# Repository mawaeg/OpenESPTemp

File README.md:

# OpenESPTemp

**OpenESPTemp** is an open-source, battery-powered temperature and environmental monitoring sensor built using an ESP32-C6 and a BME280 sensor. It is designed for integration into IoT systems.

The PCB is designed to operate with a rechargeable LiFePo4 AA battery. This repository includes the PCB design, a 3D-printable case, and basic firmware.

<div style="display: flex;">

</div>

---

## ✨ Features

- **Temperature Monitoring**: Provides readings using the BME280 sensor.
- **Environmental Sensing**: Includes humidity and pressure measurements.
- **Low Power**: Optimized for battery-powered operation (under 200nA power consumption while sleeping).
- **Battery Monitoring**: Allows monitoring of the battery voltage.
- **ESP32-C6 Microcontroller**: Handles wireless communication and processing.
- **Customizable PCB**: Features a Qwiic connector and the option to use an LDO when not using a LiFePo4 battery.
- **Open Source**: Fully customizable for specific use cases.
- **OTA updates**: Possibility to update the firmware over the air using ElegantOTA

---

## 🚀 Getting Started

### 1. The PCB

The PCB can be ordered from any PCB manufacturer (e.g., JLCPCB). It can be ordered as single boards or in panels of 5.

- **Manufacturing Files & BOM**: Included in the latest release. The Interactive HTML BOM (iBOM) is recommended for manual assembly.
- **SMT Assembly**: If using an SMT service, you will need to generate the BOM and position files yourself.

> **💡 Note:** You will need two Keystone 53 battery contacts; the BOM only mentions one.

### 2. Additional Parts

| Part | Quantity | Recommendation / Link | Note |
| :--- | :---: | :--- | :--- |
| **LiFePo4 AA (14500) battery (!Normal AA batteries won't work!)** | 1 | [LiFePo4 battery](https://de.aliexpress.com/item/1005005870958670.html?spm=a2g0o.store_pc_home.promoteWysiwyg_2003671164534.1005005870958670&gatewayAdapt=glo2deu) | Any 3.2V LiFePo4 battery should work |
| **3D Printing Filament (PETG)** | ~50g | [White PETG Filament](https://www.nobufil.com/product-page/filament-petg-white) | |
| **UART to USB Adapter** | 1 | [CP2102 Adapter](https://de.aliexpress.com/item/1005006742102516.html?pdp_npi=4%40dis%21EUR%21%E2%82%AC%201%2C97%21%E2%82%AC%200%2C99%21%21%212.28%211.14%21%40211b876717711633668585571ecf24%2112000038159199244%21sh%21DE%210%21X&spm=a2g0o.store_pc_allItems_or_groupList.new_all_items_2007567450475.1005006742102516&gatewayAdapt=glo2deu) | |
| **Pogo Pin Adapter** *(Optional)* | 1 | [4-Pin Prototyping Clamps](https://de.aliexpress.com/item/1005007887384238.html?pdp_npi=4%40dis%21EUR%21%E2%82%AC%2014%2C91%21%E2%82%AC%209%2C69%21%21%21119.18%2177.45%21%4021039ceb17711632823162636ed91c%2112000042738795008%21sh%21DE%216135611440%21X&spm=a2g0o.store_pc_home.allitems_choice_2009265069263.1005007887384238&gatewayAdapt=glo2deu) | Avoids soldering to test points. |

---

## 🛠️ Hardware Assembly

1. **Prepare the PCB**: Solder the components onto the PCB (if not using an SMT service).
   > **ℹ️ Info:** The LDO Solder Jumper is pre-closed for LiFePO4 battery use. If you choose to install an LDO, ensure you cut/open the jumper first.

   > **💡 Note:** If using a Pogo Adapter to flash the firmware, it should be flashed before mounting the battery holders, as the battery holder blocks access to the pins with the adapter.
2. **Print the Case**: Print using standard settings with a 0.2 mm layer height -  no supports needed.
   - The case does not require any screws, it holds together with snap connections
3. **Flash the Firmware**: Follow the instructions below to flash, and configure Wi-Fi/REST endpoint.
4. **Insert the Battery**:
   > **🛑 Warning:** Check the polarity carefully. Never connect the USB to UART adapter and the battery at the same time.
5. **Wake**: Press the WAK button for about a second. The sensor will start sending data periodically.

<div style="display: flex; gap: 20px;">

</div>

---

## 💻 Firmware

By default, the sensor connects to a specified Wi-Fi network and sends data to a REST API endpoint every 15 minutes.

The firmware also allows to update itself using Over The Air updates using [ElegantOTA](https://github.com/ayushsharma82/ElegantOTA).
Read more about that [here](#flash-using-ota-update).

> **💡 Note:** Newer [releases](https://github.com/mawaeg/OpenESPTemp/releases) include a pre-compiled `.bin` file. If you use this, you can skip the compilation step.

### Compiling (PlatformIO)

The firmware can be compiled and flashed with [PlatformIO](https://platformio.org/). You can build in debug mode (to get Serial debug information) or release mode:

```bash
# Debug mode
platformio run --environment esp32-c6-debug

# Release mode
platformio run --environment esp32-c6
```

The firmware has to be flashed via the Serial Interface once. Afterwards it can be updated with [OTA updates](#flash-using-ota-update).

### Flashing

**Wiring:** Connect the UART to USB adapter to the PCB:

| UART Adapter | Direction | PCB | Note |
| :--- | :---: | :--- | :--- |
| **3V3** | ⟷ | **3V3** | Use 3.3V only (do not use 5V) |
| **GND** | ⟷ | **GND** | Common ground is required |
| **TX** | ⟶ | **RX** | Connect Transmit to Receive |
| **RX** | ⟵ | **TX** | Connect Receive to Transmit |

> **ℹ️ Info:** Remember to **cross** the data lines! The **TX** (Transmit) pin on the adapter must connect to the **RX** (Receive) pin on the PCB, and vice versa.

> **🛑 Warning:** You must disconnect the battery before connecting the UART to USB adapter!

#### Option A: Flashing via PlatformIO
Run the following command:
```bash
platformio run --target upload --environment esp32-c6
```
When `Looking for upload port...` appears in the console, put the ESP32 into boot mode:
1. Push the Reset and Boot buttons at the same time.
2. Release the Reset button while keeping the Boot button pressed.
3. The upload will start; release the Boot button.

#### Option B: Flashing via esptool (Precompiled Binary)
Flash the binary using [esptool](https://github.com/espressif/esptool):
```bash
python -m esptool --chip esp32-c6 --port <your-port> --baud 460800 write_flash -z 0x1000 firmware.bin
```
*(Put the ESP32 into boot mode as described above, and replace `<your-port>` with the correct serial port.)*

### Flash using OTA update

The firmware allows to update itself via OTA updates. For that to work the firmware has to be flashed via UART initially.

This is how to trigger a OTA update.
1. Follow steps 1 and 2 of [Reconfigure the device](#reconfigure-the-device)
4. Open **`http://192.168.4.1/update`** in a browser.
5. Here you can upload a new binary (Either get it from the [releases page](https://github.com/mawaeg/OpenESPTemp/releases) or compile it yourself as described [here](#compiling-(platformio))).
6. When uploading while powered by battery you should press and hold the WAK button during the update

---

## ⚙️ Configuration

After flashing, press the Reset button once to start the firmware. If unconfigured, the device will create a Wi-Fi network for setup:

1. Connect to the **`OpenESPTemp Configurator`** Wi-Fi network.
2. Open **`http://192.168.4.1`** in a browser.
3. Configure the following fields in the form:
   - **SSID**: Target Wi-Fi network name.
   - **Password**: Target Wi-Fi network password.
   - **Post URL**: The URL for the POST request.
   - **Authorization**: The Bearer token for authentication (do not include "Bearer", only the token).
4. Click submit. The configuration will be saved, and the device will restart.
5. The sensor will now operate as expected.

### Reconfigure the device

To reconfigure the OpenESPTemp after it has already been configured once, you need do the following:
1. Bring the OpenESPTemp in config mode:
   1. When connected to UART: Press and hold FCT button and press RST shortly. Release FCT after ~6 seconds
   2. When running with battery: Press and hold FCT button and press WAK for around a second. Release FCT after ~6 seconds
2. The OpenESPTemp will create a network called  **`OpenESPTemp Configurator`**. Connect to it.
3. Open **`http://192.168.4.1`** in a browser an reconfigure the fields. Refer to [⚙️ Configuration](#⚙️-configuration)

---

## ⚡ Power consumption

The OpenESPTemp aims to have a very low power consumption.

During sleep, the power consumption is below 200nA (200nA is the limit of the PPK 2, it is probably at around 50nA according to the RV3028-C7 datasheet):

The power consumption for a whole cycle (15 min with sending data once) looks like this:

The power consumption for active mode (sending data) looks the following:

---

## 📐 PCB Design

The PCB was created using KiCad 9.0, the project files are located under [/electronics](/electronics).

The power latch used in this design was inspired by [this](https://circuitcellar.com/resources/quickbits/soft-latching-power-circuits/) article.

To generate a panel yourself using the provided script:
1. Install [KiKit](https://github.com/yaqwsx/KiKit).
2. Execute `/electronics/panelize.sh`.

The panel with the existing config looks like this:

---

## 🧊 CAD

The case was created using Onshape. To edit the case yourself click [here](https://cad.onshape.com/documents/398f777c8db5f4a69ffcddaa/w/b07485d077929fc2f0119cac/e/3395ca67b8682bc329248728?configuration=List_Cy8et1WFmB3Iby%3DDefault&renderMode=0&uiState=699202edfa46508150bca706) and copy the project.

The current STL files are included in the repo under [/cad](/cad).

---

## 🚧 Troubleshooting

TBD

---

## 🗺️ Coming Next

- [ ] Include mounting bracket for the case
- [ ] Include HomeAssistant integration

---

## 📄 License

This project is licensed under the GNU General Public License v3.0. See the [LICENSE](LICENSE) file for details.

### Hardware Libraries
Various libraries were used to create the PCB. Copies of most libraries are included in `/electronics/libs/` to ensure the KiCad project works without manual installation.

Some of these libraries are licensed under their respective licenses. Please review the `README.md` file in the library folders.

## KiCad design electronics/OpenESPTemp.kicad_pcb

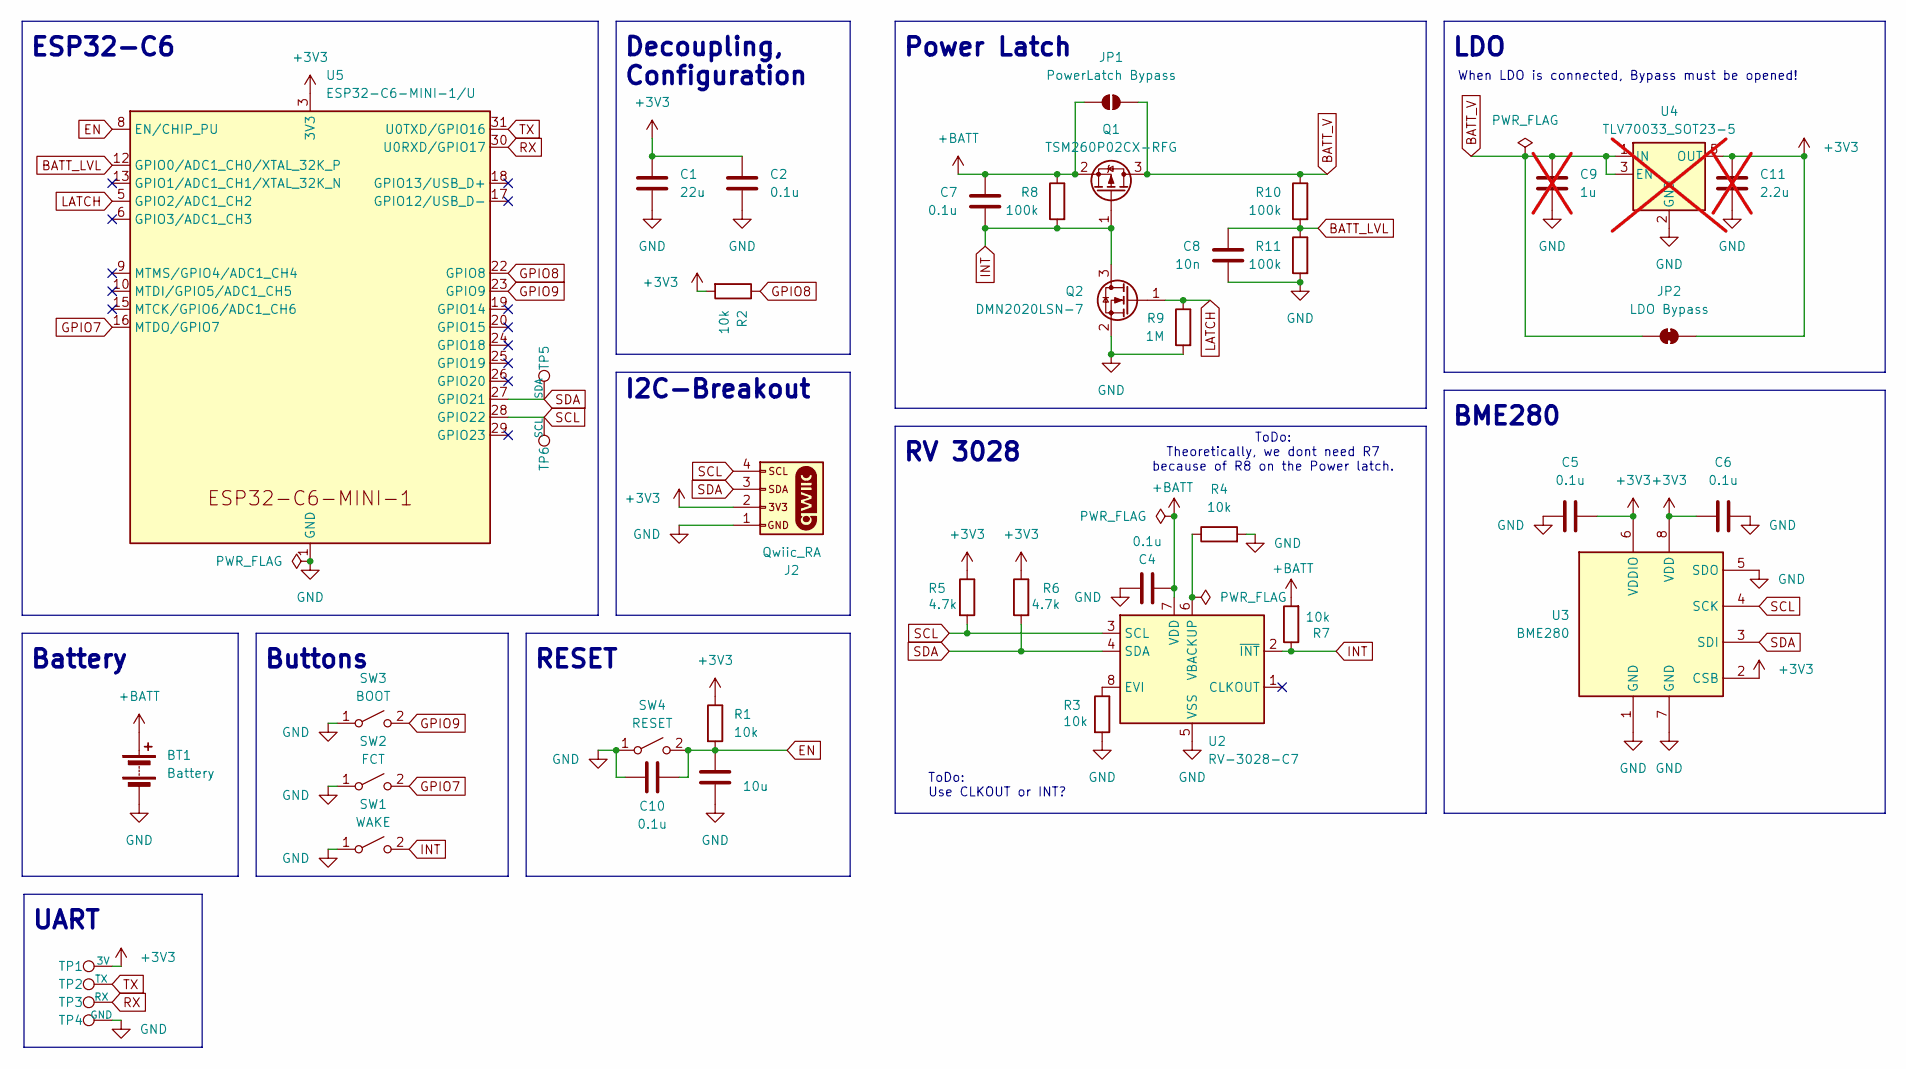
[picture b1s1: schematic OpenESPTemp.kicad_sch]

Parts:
BT1: Battery; Keystone_53_Dual
C1: 22u; C_0603_1608Metric
C2, C4, C5, C6, C7, C10: 0.1u; C_0603_1608Metric
C3: 10u; C_0603_1608Metric
C8: 10n; C_0603_1608Metric
C9: 1u; C_0603_1608Metric; not fitted
C11: 2.2u; C_0603_1608Metric; not fitted
J2: Qwiic_RA; JST_1x04_P1.0mm_Horizontal_SMD
JP1: PowerLatch Bypass; SolderJumper-2_P1.3mm_Open_RoundedPad1.0x1.5mm
JP2: LDO Bypass; SolderJumper-2_P1.3mm_Bridged_RoundedPad1.0x1.5mm
Q1: TSM260P02CX-RFG; SOT-23
Q2: DMN2020LSN-7; SOT-23
R1, R2, R3, R4, R7: 10k; R_0603_1608Metric
R5, R6: 4.7k; R_0603_1608Metric
R8, R10, R11: 100k; R_0603_1608Metric
R9: 1M; R_0603_1608Metric
SW1: WAKE; SW_SPST_B3U-1000P
SW2: FCT; SW_SPST_B3U-1000P
SW3: BOOT; SW_SPST_B3U-1000P
SW4: RESET; SW_SPST_B3U-1000P
TP1: 3V; TestPoint_Pad_D1.5mm
TP2: TX; TestPoint_Pad_D1.5mm
TP3: RX; TestPoint_Pad_D1.5mm
TP4: GND; TestPoint_Pad_D1.5mm
TP5: SDA; TestPoint_Pad_D1.5mm
TP6: SCL; TestPoint_Pad_D1.5mm
U2: RV-3028-C7; MicroCrystal_C7_SON-8_1.5x3.2mm_P0.9mm
U3: BME280; Bosch_LGA-8_2.5x2.5mm_P0.65mm_ClockwisePinNumbering
U4: TLV70033_SOT23-5; SOT-23-5; not fitted
U5: ESP32-C6-MINI-1/U; ESP32-C6-MINI-1

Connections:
+3V3: C1.1, C2.1, C5.2, C6.1, C11.1, J2.2, JP2.2 (B), R1.1, R2.2, R5.1, R6.1, TP1.1, U3.2 (CSB), U3.6 (VDDIO), U3.8 (VDD), U4.5 (OUT), U5.3 (3V3)
+BATT: BT1.1 (+), C4.1, C7.1, JP1.1 (A), Q1.2 (S), R7.2, R8.1, U2.7 (VDD)
BATT_LVL: C8.1, R10.2, R11.1, U5.12 (GPIO0/ADC1_CH0/XTAL_32K_P)
BATT_V: C9.1, JP1.2 (B), JP2.1 (A), Q1.3 (D), R10.1, U4.1 (IN), U4.3 (EN)
EN: C3.1, C10.1, R1.2, SW4.2 (B), U5.8 (EN/CHIP_PU)
GND: BT1.2 (-), C1.2, C2.2, C3.2, C4.2, C5.1, C6.2, C8.2, C9.2, C10.2, C11.2, J2.1, Q2.2 (S), R3.2, R4.2, R9.2, R11.2, SW1.1 (A), SW2.1 (A), SW3.1 (A), SW4.1 (A), TP4.1, U2.5 (VSS), U3.1 (GND), U3.5 (SDO), U3.7 (GND), U4.2 (GND), U5.1 (GND), U5.2 (GND), U5.11 (GND), U5.14 (GND), U5.36 (GND), U5.37 (GND), U5.38 (GND), U5.39 (GND), U5.40 (GND), U5.41 (GND), U5.42 (GND), U5.43 (GND), U5.44 (GND), U5.45 (GND), U5.46 (GND), U5.47 (GND), U5.48 (GND), U5.49 (GND), U5.50 (GND), U5.51 (GND), U5.52 (GND), U5.53 (GND)
GPIO7: SW2.2 (B), U5.16 (MTDO/GPIO7)
GPIO8: R2.1, U5.22 (GPIO8)
GPIO9: SW3.2 (B), U5.23 (GPIO9)
INT: C7.2, Q1.1 (G), Q2.3 (D), R7.1, R8.2, SW1.2 (B), U2.2 (~INT)
LATCH: Q2.1 (G), R9.1, U5.5 (GPIO2/ADC1_CH2)
unnamed: R3.1, U2.8 (EVI)
unnamed: R4.1, U2.6 (VBACKUP)
RX: TP3.1, U5.30 (U0RXD/GPIO17)
SCL: J2.4, R5.2, TP6.1, U2.3 (SCL), U3.4 (SCK), U5.28 (GPIO22)
SDA: J2.3, R6.2, TP5.1, U2.4 (SDA), U3.3 (SDI), U5.27 (GPIO21)
TX: TP2.1, U5.31 (U0TXD/GPIO16)

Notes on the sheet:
Power Latch
I2C-Breakout
Decoupling, Configuration
ToDo: Theoretically, we dont need R7 because of R8 on the Power latch.
RV 3028
When LDO is connected, Bypass must be opened!
ESP32-C6
LDO
Buttons
BME280
RESET
Battery
ToDo: Use CLKOUT or INT?
UART

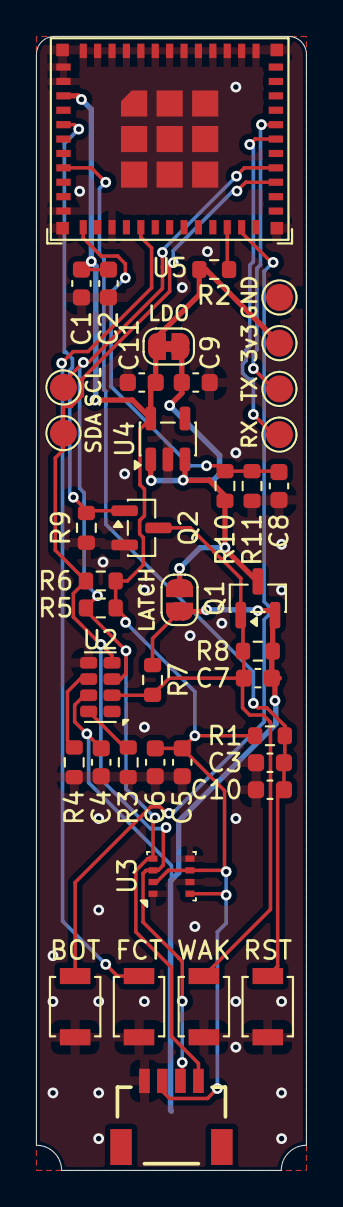
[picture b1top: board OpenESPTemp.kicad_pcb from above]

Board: 2 copper layers, 15.0 x 63.0 mm, 42 parts (1 on the bottom side), 17 nets.

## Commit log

2024-12-25 Update Readme for newest pcb version
2024-12-27 Update copy of pcb Also updated images and readme accordingly
2024-12-27 Update coming next in readme
2025-09-30 Implement webserver for firmware configuration These firmware changes implement a webserver for configuring WiFi and POST request which was previously done via the SECRETS.h file. For saving the cred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
2025-12-27 Update firmware for new pcb
    - Migrate to esp32-c6 (uses pioarduino instead of platformio to have
    arduino support for esp32-c6)
    - Updates the pins used
    - integrates support for the Power Latch mechanism
2025-12-27 Initial Kicad PCB version
    This moves the PCB to a Kicad project.
    It also introduces a Power Latch triggered by an UltraLowPowerTimer to
    reduce power consumption
2025-12-27 Document configuration with webserver in README
2025-12-27 Update firmware dependencies
    Updates AsyncWebServer dependency and fixes error when compiling (with pioarduino)
2025-12-27 Describe flashing precompiled binary with esptool.py
2025-12-27 Fix merge error
2026-02-03 Adding reset option with FCT button
    - When the button is pressed and hold for 5 seconds after the reset the stored credentials will be deleted
    - Button must already be pressed while resetting.
2026-02-13 Minor improvements
2026-02-15 Adapt README to new hardware revision
2026-02-15 Update images
2026-02-15 Update case stl files
2026-02-15 Improve UART to USB wiring description
2026-02-16 Fix Pcb issues
    - Fix wrong connection of C4
    - Move symbol lib into libs/; Delete unused .kicad_sch file
    - Make LDO Solder Jumper Bridged by default
    - Fix temp notes file (Licenses.txt)
2026-02-17 Improve firmware
    - Configuring timer was done after wifi connection -> If no Wifi connection was established, ESP would sleep forever, this is now fixed
    - After the configServer ran, the CLKOUT of the RV3028 is now disabled to reduce power consumption
    - Remove stop_wifi(), as it just takes time and esp powers done completely nevertheless
2026-02-17 Add OTA support to firmware
    - Adds support for OTA using ElegantOTA
2026-02-17 Add power consumption section to README
2026-02-27 fix(electronics): Improve Schematic
    Improve schematic overall
    Add exported .pdf of current schematics
2026-02-27 fix(docs): Remove hardware fix section
